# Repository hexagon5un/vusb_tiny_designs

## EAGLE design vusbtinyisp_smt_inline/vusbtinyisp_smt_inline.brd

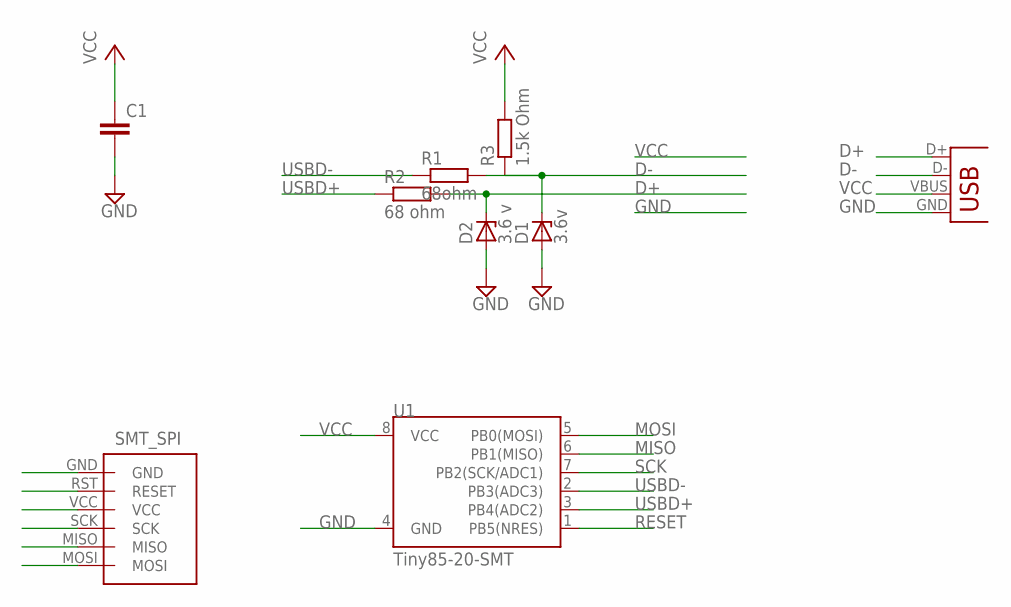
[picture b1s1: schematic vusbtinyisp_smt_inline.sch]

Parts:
C1: CAP1206; 1206
D1: 3.6v; SOT23
D2: 3.6 v; SOT23
JP2: USBSMD; USB-MINIB
R1: 68ohm; R0805
R2: 68 ohm; R0805
R3: 1.5k Ohm; R1206
U1: Tiny85-20-SMT; SO08-EIAJ
U$1: SMT_ISP; SMT_PADS

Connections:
D+: D2.3 (C), JP2.D+, R2.2
D-: D1.3 (C), JP2.D-, R1.2, R3.1
GND: C1.2, D1.1 (A), D2.1 (A), JP2.GND, U1.4 (GND), U$1.GND
MISO: U1.6 (PB1(MISO)), U$1.MISO
MOSI: U1.5 (PB0(MOSI)), U$1.MOSI
RESET: U1.1 (PB5(NRES)), U$1.RST (RESET)
SCK: U1.7 (PB2(SCK/ADC1)), U$1.SCK
USBD+: R2.1, U1.3 (PB4(ADC2))
USBD-: R1.1, U1.2 (PB3(ADC3))
VCC: C1.1, JP2.VBUS, R3.2, U1.8 (VCC), U$1.VCC

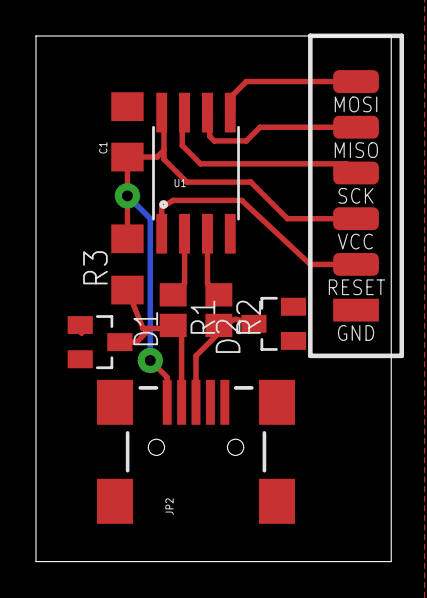
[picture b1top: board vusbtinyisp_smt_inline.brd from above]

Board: 2 copper layers, 19.7 x 29.2 mm, 9 parts (0 on the bottom side), 10 nets.

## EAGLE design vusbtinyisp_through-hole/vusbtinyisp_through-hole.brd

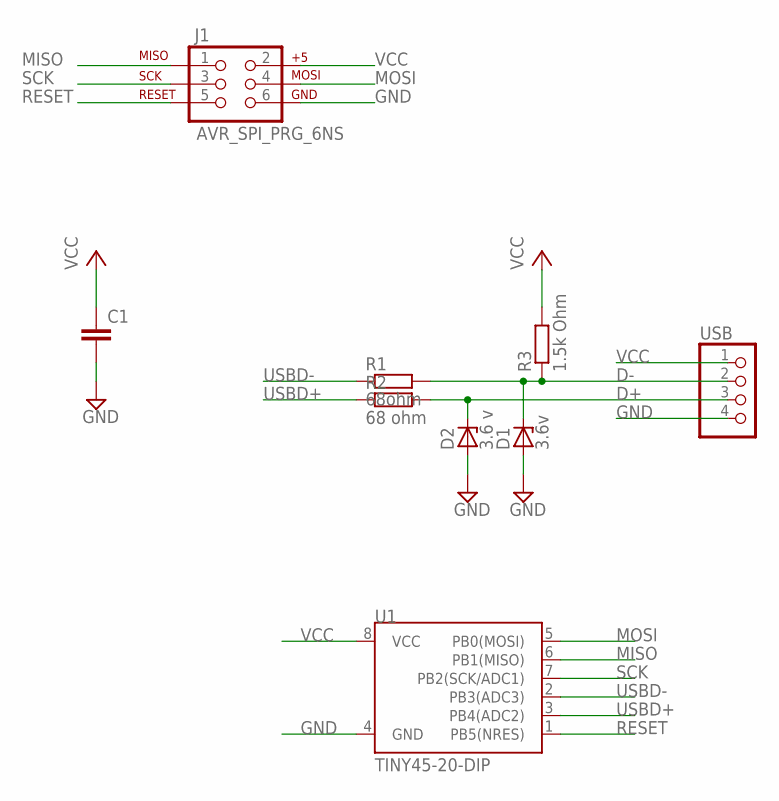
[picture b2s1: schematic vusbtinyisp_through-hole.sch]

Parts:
C1: CAPPTH; CAP-PTH-SMALL
D1: 3.6v; DO35Z10
D2: 3.6 v; DO35Z10
J1: AVR_SPI_PRG_6NS; 2X3-NS
R1: 68ohm; 0207/10
R2: 68 ohm; 0207/10
R3: 1.5k Ohm; 0207/10
U1: TINY45-20-DIP; DIP08
USB: PINHD-1X4; 1X04

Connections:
D+: D2.C, R2.2, USB.3
D-: D1.C, R1.2, R3.1, USB.2
GND: C1.2, D1.A, D2.A, J1.6, U1.4 (GND), USB.4
MISO: J1.1, U1.6 (PB1(MISO))
MOSI: J1.4, U1.5 (PB0(MOSI))
RESET: J1.5, U1.1 (PB5(NRES))
SCK: J1.3, U1.7 (PB2(SCK/ADC1))
USBD+: R2.1, U1.3 (PB4(ADC2))
USBD-: R1.1, U1.2 (PB3(ADC3))
VCC: C1.1, J1.2, R3.2, U1.8 (VCC), USB.1

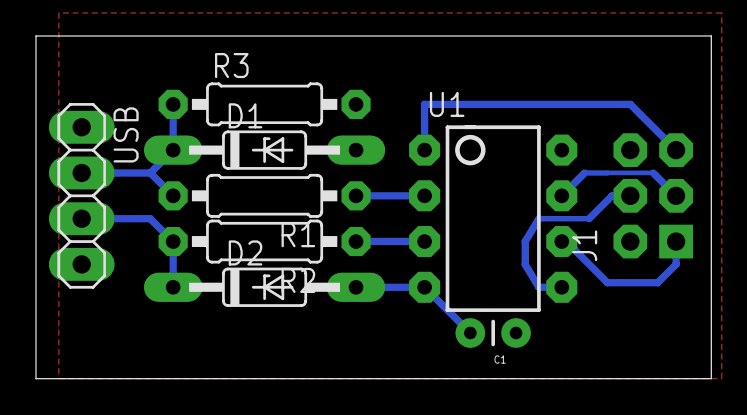
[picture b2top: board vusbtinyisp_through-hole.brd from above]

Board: 2 copper layers, 37.5 x 19.0 mm, 9 parts (0 on the bottom side), 10 nets.

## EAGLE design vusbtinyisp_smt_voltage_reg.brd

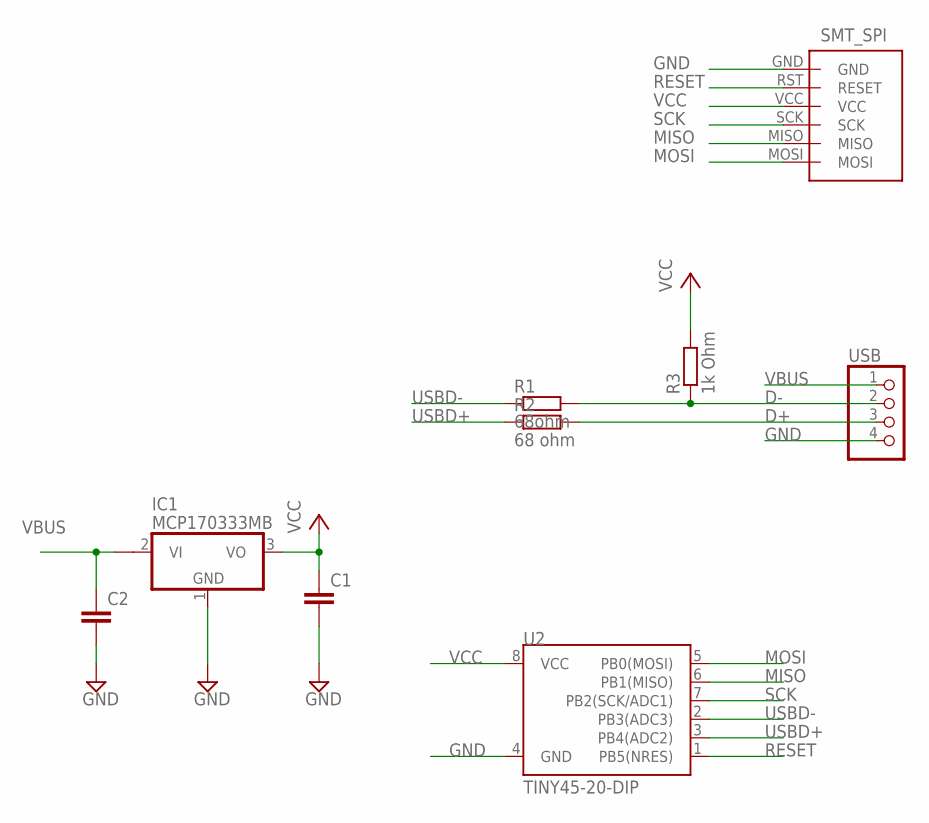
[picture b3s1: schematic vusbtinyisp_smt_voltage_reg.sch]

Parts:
C1, C2: CAP1206; 1206
IC1: MCP170333MB; SOT89
R1: 68ohm; R0805
R2: 68 ohm; R0805
R3: 1k Ohm; R1206
U2: TINY45-20-DIP; DIP08
U$1: SMT_ISP; SMT_PADS
USB: PINHD-1X4; 1X04

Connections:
D+: R2.2, USB.3
D-: R1.2, R3.1, USB.2
GND: C1.2, C2.2, IC1.1 (GND), U2.4 (GND), U$1.GND, USB.4
MISO: U2.6 (PB1(MISO)), U$1.MISO
MOSI: U2.5 (PB0(MOSI)), U$1.MOSI
RESET: U2.1 (PB5(NRES)), U$1.RST (RESET)
SCK: U2.7 (PB2(SCK/ADC1)), U$1.SCK
USBD+: R2.1, U2.3 (PB4(ADC2))
USBD-: R1.1, U2.2 (PB3(ADC3))
VBUS: C2.1, IC1.2@1 (VI1), USB.1
VCC: C1.1, IC1.3 (VO), R3.2, U2.8 (VCC), U$1.VCC

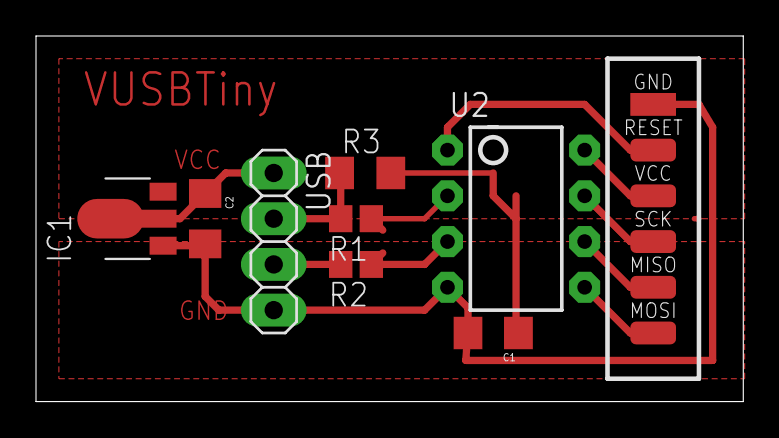
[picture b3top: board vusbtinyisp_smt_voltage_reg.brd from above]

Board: 2 copper layers, 39.3 x 20.3 mm, 9 parts (0 on the bottom side), 11 nets.

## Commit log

2014-07-21 initial commit -- SMT/VR version
2014-07-21 set up versions for tweakification
    these are all clones of the trunk SMT version
    change parts to fit
2014-07-21 complete, untested dip version
2014-07-22 Added readme and PDF schematics
2014-07-22 changing 1k to 1.5k resistors in 5V designs
2014-07-22 moving all files to their own directories
2014-07-22 Created Gerbers and toner-transfer files
2014-07-22 note in readme about gerbers, silkscreens
2014-07-22 links to my website, added photo, teaser for Make

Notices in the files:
parts and their libraries:
SparkFun-DigitalIC: Licensing: CC v3.0 Share-Alike You are welcome to use this library for commercial purposes.
